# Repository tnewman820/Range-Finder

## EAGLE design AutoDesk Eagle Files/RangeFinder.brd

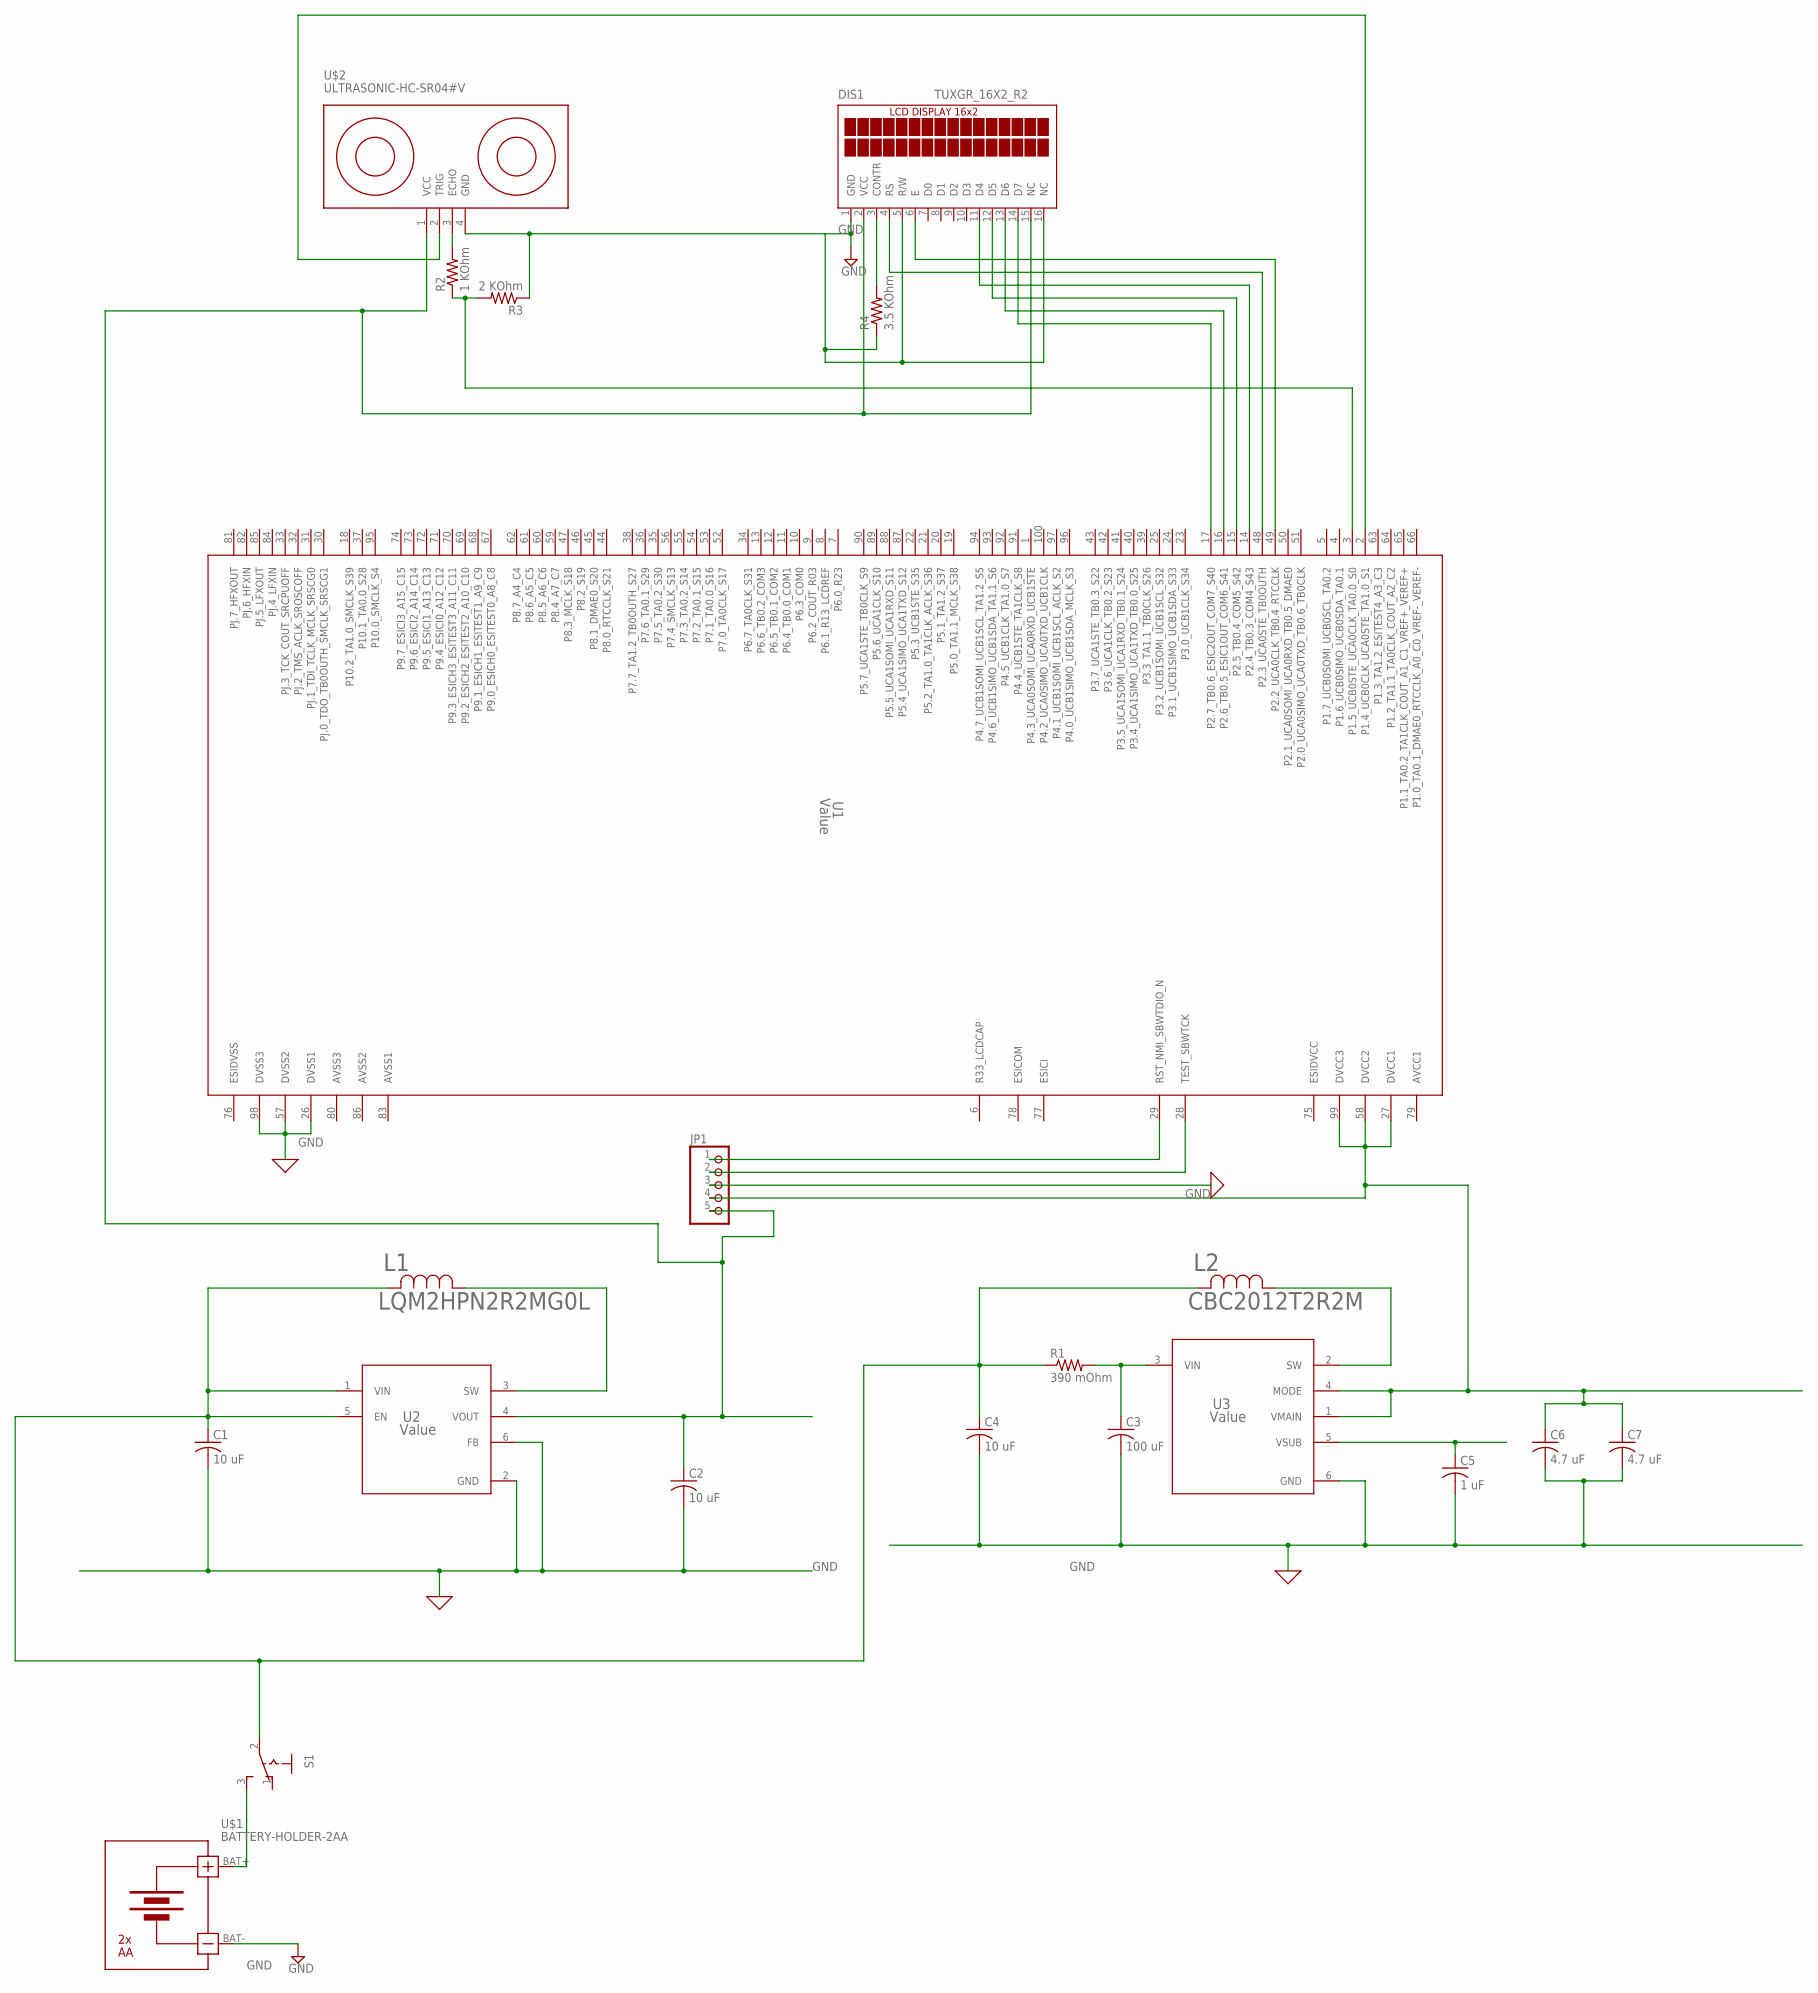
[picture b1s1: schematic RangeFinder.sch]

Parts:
C1, C2, C4: 10 uF; C0805; MPN TMK212BBJ106MG-T
C3: 100 uF; C0805; MPN PMK212BBJ107MG-T.
C5: 1 uF; C0805; MPN MC0805F105Z500CT
C6, C7: 4.7 uF; C0805; MPN TMK212BBJ106MG-T
DIS1: TUXGR_16X2_R2; MPN MC21605C6W-BNMLW-V2
JP1: PINHD-1X5; 1X05; MPN 2211S-05G
L1: LQM2HPN2R2MG0L; IND_LQM2HPN2R2MG0L_MUR; MPN LQM2HPN2R2MG0L
L2: CBC2012T2R2M; IND_TAIYO_CBC2012_TAY; MPN CBC2012T2R2M.
R1: 390 mOhm; R0805; MPN ERJ-6DQJR39V
R2: 1 KOhm; R0805; MPN MCPWR05FTEW1001
R3: 2 KOhm; R0805; MPN ERA-6AEB202V
R4: 3.5 KOhm; R0805; MPN PCF0805R-3K57BT1
S1: 255SB; MPN EG1218
U1: Value; PZ0100A_L; MPN MSP432P401RIPZR
U2: Value; YFF0006AFAD
U3: Value; DSE0006A
U$1: BATTERY-HOLDER-2AA; MPN 2462
U$2: ULTRASONIC-HC-SR04#V; MPN 83-17989

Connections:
unnamed: C3.1, R1.2, U3.3 (VIN)
unnamed: S1.3 (S), U$1.BAT+
unnamed: C5.1, U3.5 (VSUB)
unnamed: C1.1, C4.1, L1.2, L2.2, R1.1, S1.2, U2.1 (VIN), U2.5 (EN)
unnamed: C6.1, C7.1, JP1.4, U1.27 (DVCC1), U1.58 (DVCC2), U1.75 (ESIDVCC), U1.79 (AVCC1), U1.99 (DVCC3), U3.1 (VMAIN), U3.4 (MODE)
unnamed: JP1.1, U1.29 (RST_NMI_SBWTDIO_N)
unnamed: L2.1, U3.2 (SW)
unnamed: JP1.2, U1.28 (TEST_SBWTCK)
unnamed: R2.1, R3.2, U1.3 (P1.5_UCB0STE_UCA0CLK_TA0.0_S0)
unnamed: L1.1, U2.3 (SW)
unnamed: R2.2, U$2.3 (ECHO)
unnamed: DIS1.3 (CONTR), R4.2
unnamed: U1.2 (P1.4_UCB0CLK_UCA0STE_TA1.0_S1), U$2.2 (TRIG)
unnamed: DIS1.11 (D4), U1.14 (P2.4_TB0.3_COM4_S43)
unnamed: DIS1.12 (D5), U1.15 (P2.5_TB0.4_COM5_S42)
unnamed: DIS1.13 (D6), U1.16 (P2.6_TB0.5_ESIC1OUT_COM6_S41)
unnamed: DIS1.14 (D7), U1.17 (P2.7_TB0.6_ESIC2OUT_COM7_S40)
unnamed: DIS1.6 (E), U1.49 (P2.2_UCA0CLK_TB0.4_RTCCLK)
unnamed: DIS1.4 (RS), U1.48 (P2.3_UCA0STE_TB0OUTH)
unnamed: C2.1, DIS1.2 (VCC), DIS1.15 (NC), JP1.5, U2.4 (VOUT), U$2.1 (VCC)

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
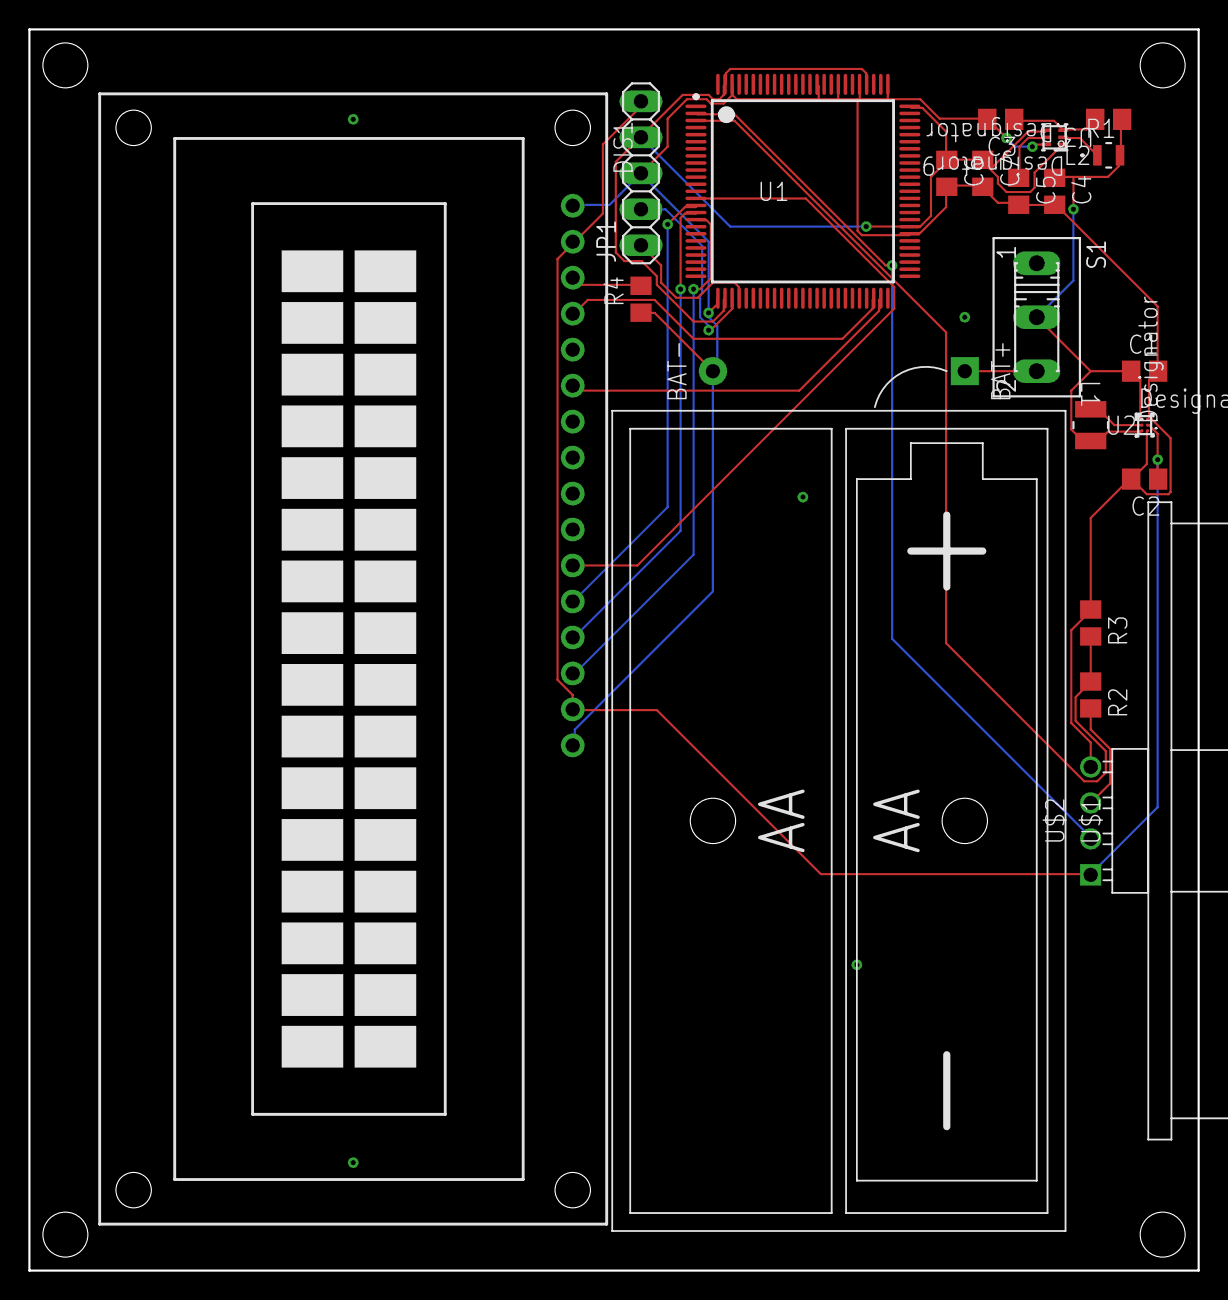
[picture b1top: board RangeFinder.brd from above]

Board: 2 copper layers, 82.5 x 87.6 mm, 21 parts (0 on the bottom side), 21 nets.

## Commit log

2021-10-27 Added AutoDesk Eagle Files
2021-10-27 Added BOM
2021-10-27 Added TI WEBENCH Files
2021-10-27 Added Images Of Both Board and Schematic

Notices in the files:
parts and their libraries:
diy-modules: Released under the Creative Commons Attribution 4.0 International License: http://creativecommons.org/licenses/by/4.0
COPYRIGHT: Copyright (C) 2018 Accelerated Designs. All rights reserved
